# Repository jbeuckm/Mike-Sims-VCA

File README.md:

**Design Ideas:January 19, 1995**

## Low-cost audio VCA has high performance ##

**Mike Sims**,
*Lectrosonics Inc, Rio Rancho, NM*

---

The inherent matching between the two transconductance amplifiers in IC<sub>1</sub> (Fig. 1) facilitates a voltage-controlled amplifier (VCA) that offers high performance and low cost. The circuits maximum input voltage is +20 dBu (dBu=dB referred to 775 mV rms). THD measures less than 0.015%; noise, -70 dBu; and control-voltage feedthrough, -70 dB.

<table>
<tr>
<td></td>
</tr>
<tr>
<td><i>Matched transconductance amplifiers enable an inexpensive voltage-controlled amplifier whose gain is linearly proportional to the control voltage.</i></td>
</tr>
</table>

The signal path is simple. IC <sub>1A</sub> negative-feedback configuration forces the current from IC<sub>1A</sub> pin 5 to equal the ac-input current through R<sub>1</sub>. IC<sub>1A</sub> pin 5 also connects to IC<sub>1B</sub> pin 13, causing a virtually identical current to flow from IC<sub>1B</sub> pin 12. IC<sub>2A</sub> converts this current to an output voltage, V<sub>OUT</sub> .

The output op amp limits the circuits maximum output voltage. (A dual FET-input op amp, such as the TL072, works well for IC<sub>2</sub>.) C<sub>1</sub> sets the circuits 3-dB bandwidth at about 40 kHz.

Varying the control current into IC<sub>1B</sub> relative to fixed current flowing through IC<sub>1A</sub> R<sub>2</sub> controls the circuits gain. R<sub>2</sub> sets the control current in IC<sub>1A</sub> to

I<sub>CONT A</sub> =(15-2V<sub>D</sub> )/R<sub>2,</sub>

which is approximately 265 &micro;A. The 2V<sub>D</sub> factor arises because the control-port voltage is two diode drops above the negative rail.

IC<sub>2B</sub> and associated components form a linear voltage-to-current converter that feeds the control port of IC<sub>1B</sub> . The control current for IC<sub>1B</sub> is 

I<sub>CONT B</sub>=V<sub>CONT</sub> /R<sub>3</sub>.

The overall circuit gain is

V<sub>OUT</sub>/V<sub>IN,</sub>=-(R<sub>4</sub>/R<sub>1</sub>) &times; (I <sub>CONTB</sub> /I<sub>CONTA</sub> ).

A 5V control signal generates unity gain. The gain is linearly proportional to the control voltage.

R<sub>2</sub> , in conjunction with R<sub>1</sub> , limits the circuits maximum input voltage to 

V <sub>INMAX</sub>=2 &times; I<sub>CONTA</sub>&times;R<sub>1</sub>,

or a peak input voltage of around 16V.

Use R<sub>5</sub> to trim the circuit for minimum THD. Trimming for minimum THD simultaneously achieves minimum control-voltage feedthrough. Interchanging pins 13 and 14 of IC<sub>1B</sub> realizes a noninverting VCA. (DI #1604)

---

*Copyright &copy; 1995 EDN Magazine. EDN is a registered trademark of Reed Properties Inc, used under license.*

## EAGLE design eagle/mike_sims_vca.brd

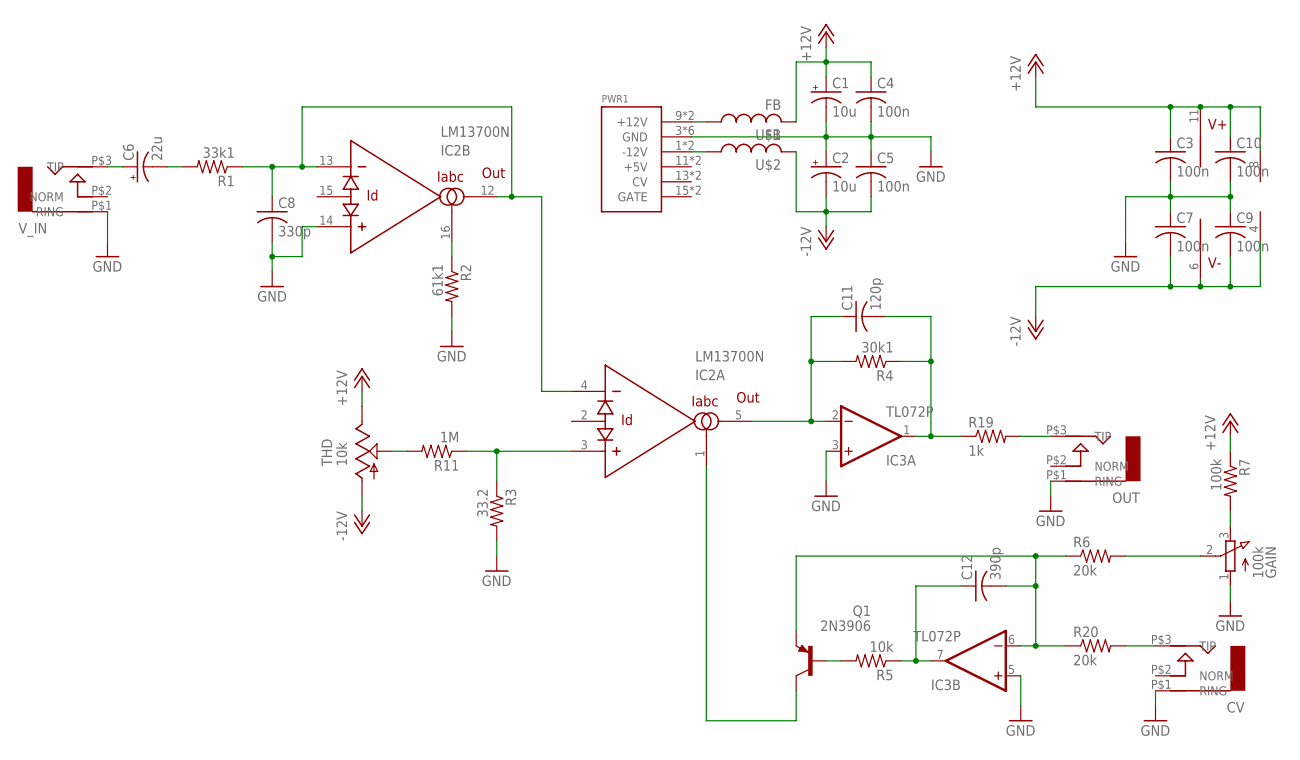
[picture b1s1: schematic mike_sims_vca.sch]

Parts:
C1, C2: 10u; B45181A
C3, C4, C5, C7, C9, C10: 100n; C050-024X044
C6: 22u; B45181A
C8: 330p; C050-024X044
C11: 120p; C050-024X044
C12: 390p; C050-024X044
CV: AUDIO-JACK; ERTHENVAR-JACK-90DEG
GAIN: 100k; 3RP/1610N
IC2: LM13700N; DIL16
IC3: TL072P; DIL08
OUT: AUDIO-JACK; ERTHENVAR-JACK-90DEG
PWR1: POWER; POWER_16
Q1: 2N3906; TO92
R1: 33k1; 0207/10
R2: 61k1; 0207/10
R3: 33.2; 0207/10
R4: 30k1; 0207/10
R5: 10k; 0207/10
R6, R20: 20k; 0207/10
R7: 100k; 0207/10
R11: 1M; 0207/10
R19: 1k; 0207/10
THD: 10k; B64Y
U$1, U$2: FB
V_IN: AUDIO-JACK; ERTHENVAR-JACK-90DEG

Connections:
+12V: C1.+, C3.1, C4.1, C10.1, IC2.11 (V+), IC3.8 (V+), R7.1, THD.E, U$1.P$2 (2)
-12V: C2.-, C5.2, C7.2, C9.2, IC2.6 (V-), IC3.4 (V-), THD.A, U$2.P$2 (2)
GND: C1.-, C2.+, C3.2, C4.2, C5.1, C7.1, C8.2, C9.1, C10.2, CV.P$1 (RING), GAIN.1 (A), IC2.14 (+IN), IC3.3 (+IN), IC3.5 (+IN), OUT.P$1 (RING), PWR1.3 (GND), PWR1.4 (GND), PWR1.5 (GND), PWR1.6 (GND), PWR1.7 (GND), PWR1.8 (GND), R2.2, R3.2, V_IN.P$1 (RING)
unnamed: PWR1.9 (+12V), PWR1.10 (+12V), U$1.P$1 (1)
unnamed: PWR1.1 (-12V), PWR1.2 (-12V), U$2.P$1 (1)
unnamed: C6.+, V_IN.P$3 (TIP)
unnamed: C6.-, R1.2
unnamed: C8.1, IC2.4 (-IN), IC2.12 (OUT), IC2.13 (-IN), R1.1
unnamed: IC2.3 (+IN), R3.1, R11.1
unnamed: IC2.16 (IABC), R2.1
unnamed: C11.2, IC3.1 (OUT), R4.1, R19.1
unnamed: C11.1, IC2.5 (OUT), IC3.2 (-IN), R4.2
unnamed: Q1.2 (B), R5.2
unnamed: C12.1, IC3.7 (OUT), R5.1
unnamed: GAIN.2 (S), R6.2
unnamed: GAIN.3 (E), R7.2
unnamed: R11.2, THD.S
unnamed: C12.2, IC3.6 (-IN), Q1.3 (E), R6.1, R20.1
unnamed: IC2.1 (IABC), Q1.1 (C)
unnamed: OUT.P$3 (TIP), R19.2
unnamed: CV.P$3 (TIP), R20.2

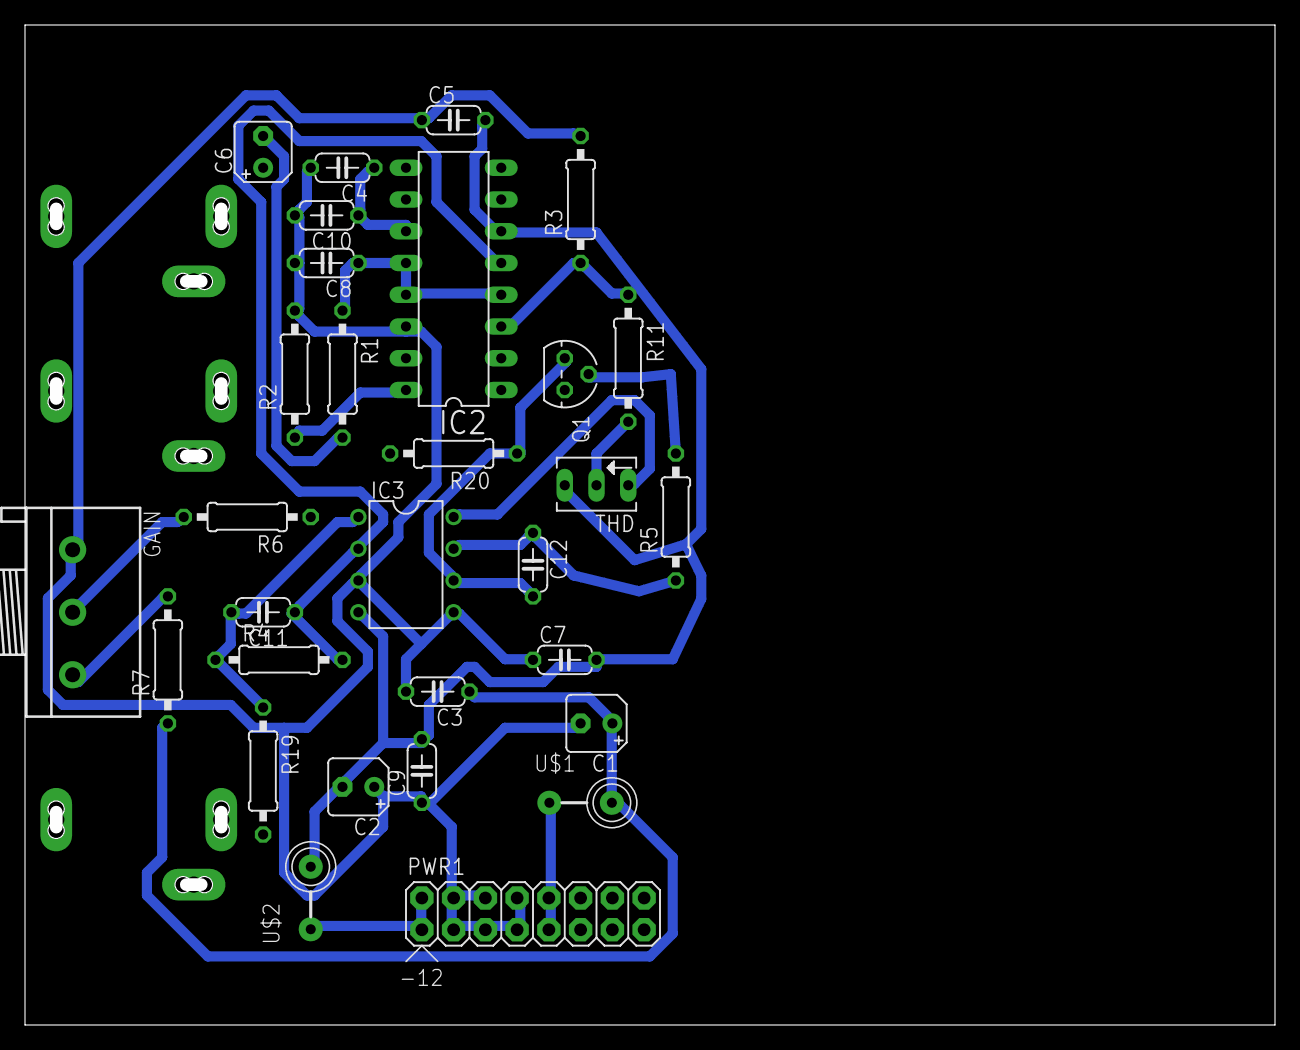
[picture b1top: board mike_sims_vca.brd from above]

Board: 2 copper layers, 99.0 x 79.0 mm, 33 parts (0 on the bottom side), 21 nets.

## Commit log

2016-01-20 schemo
2016-01-20 nearly routed
2016-01-21 moved to vertical
2016-01-22 routed
2016-01-23 gcode
2016-01-23 it works
2016-01-23 layout image
2016-01-24 panel
2018-09-12 .DS_Store
